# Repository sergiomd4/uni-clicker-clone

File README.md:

UNI Clicker Clone
========================================

UNI Clicker is a compact development board designed as a complete solution. It contains a MCU Card socket, four mikroBUS sockets for Click boards connectivity and power management. 

Its core is a MCU Card socket that allows UNI Clicker to use different microcontrollers mounted on a standardized MCU Card. The MCU Card can be connected to the UNI Clicker by two 168-pin mezzanine connectors, one male and one female. This MCU Card supports architectures such as ARM, PIC32, dsPIC, PIC, AVR, Microchip, ST, NXP, TI and more.

UNI Clicker can be powered on by a small switch at the edge of the board. Therefore, the PSU (Power Supply Unit) module will be enabled and the power will be distributed. The PWR LED indicates that the board is ON.

Repository Contents
-------------------

* **/Production** - Gerber files, drill files, BOM, CPL file
* **/Hardware** - KiCad PCB files, footprints library
* **/Documents** - Schematics pdf

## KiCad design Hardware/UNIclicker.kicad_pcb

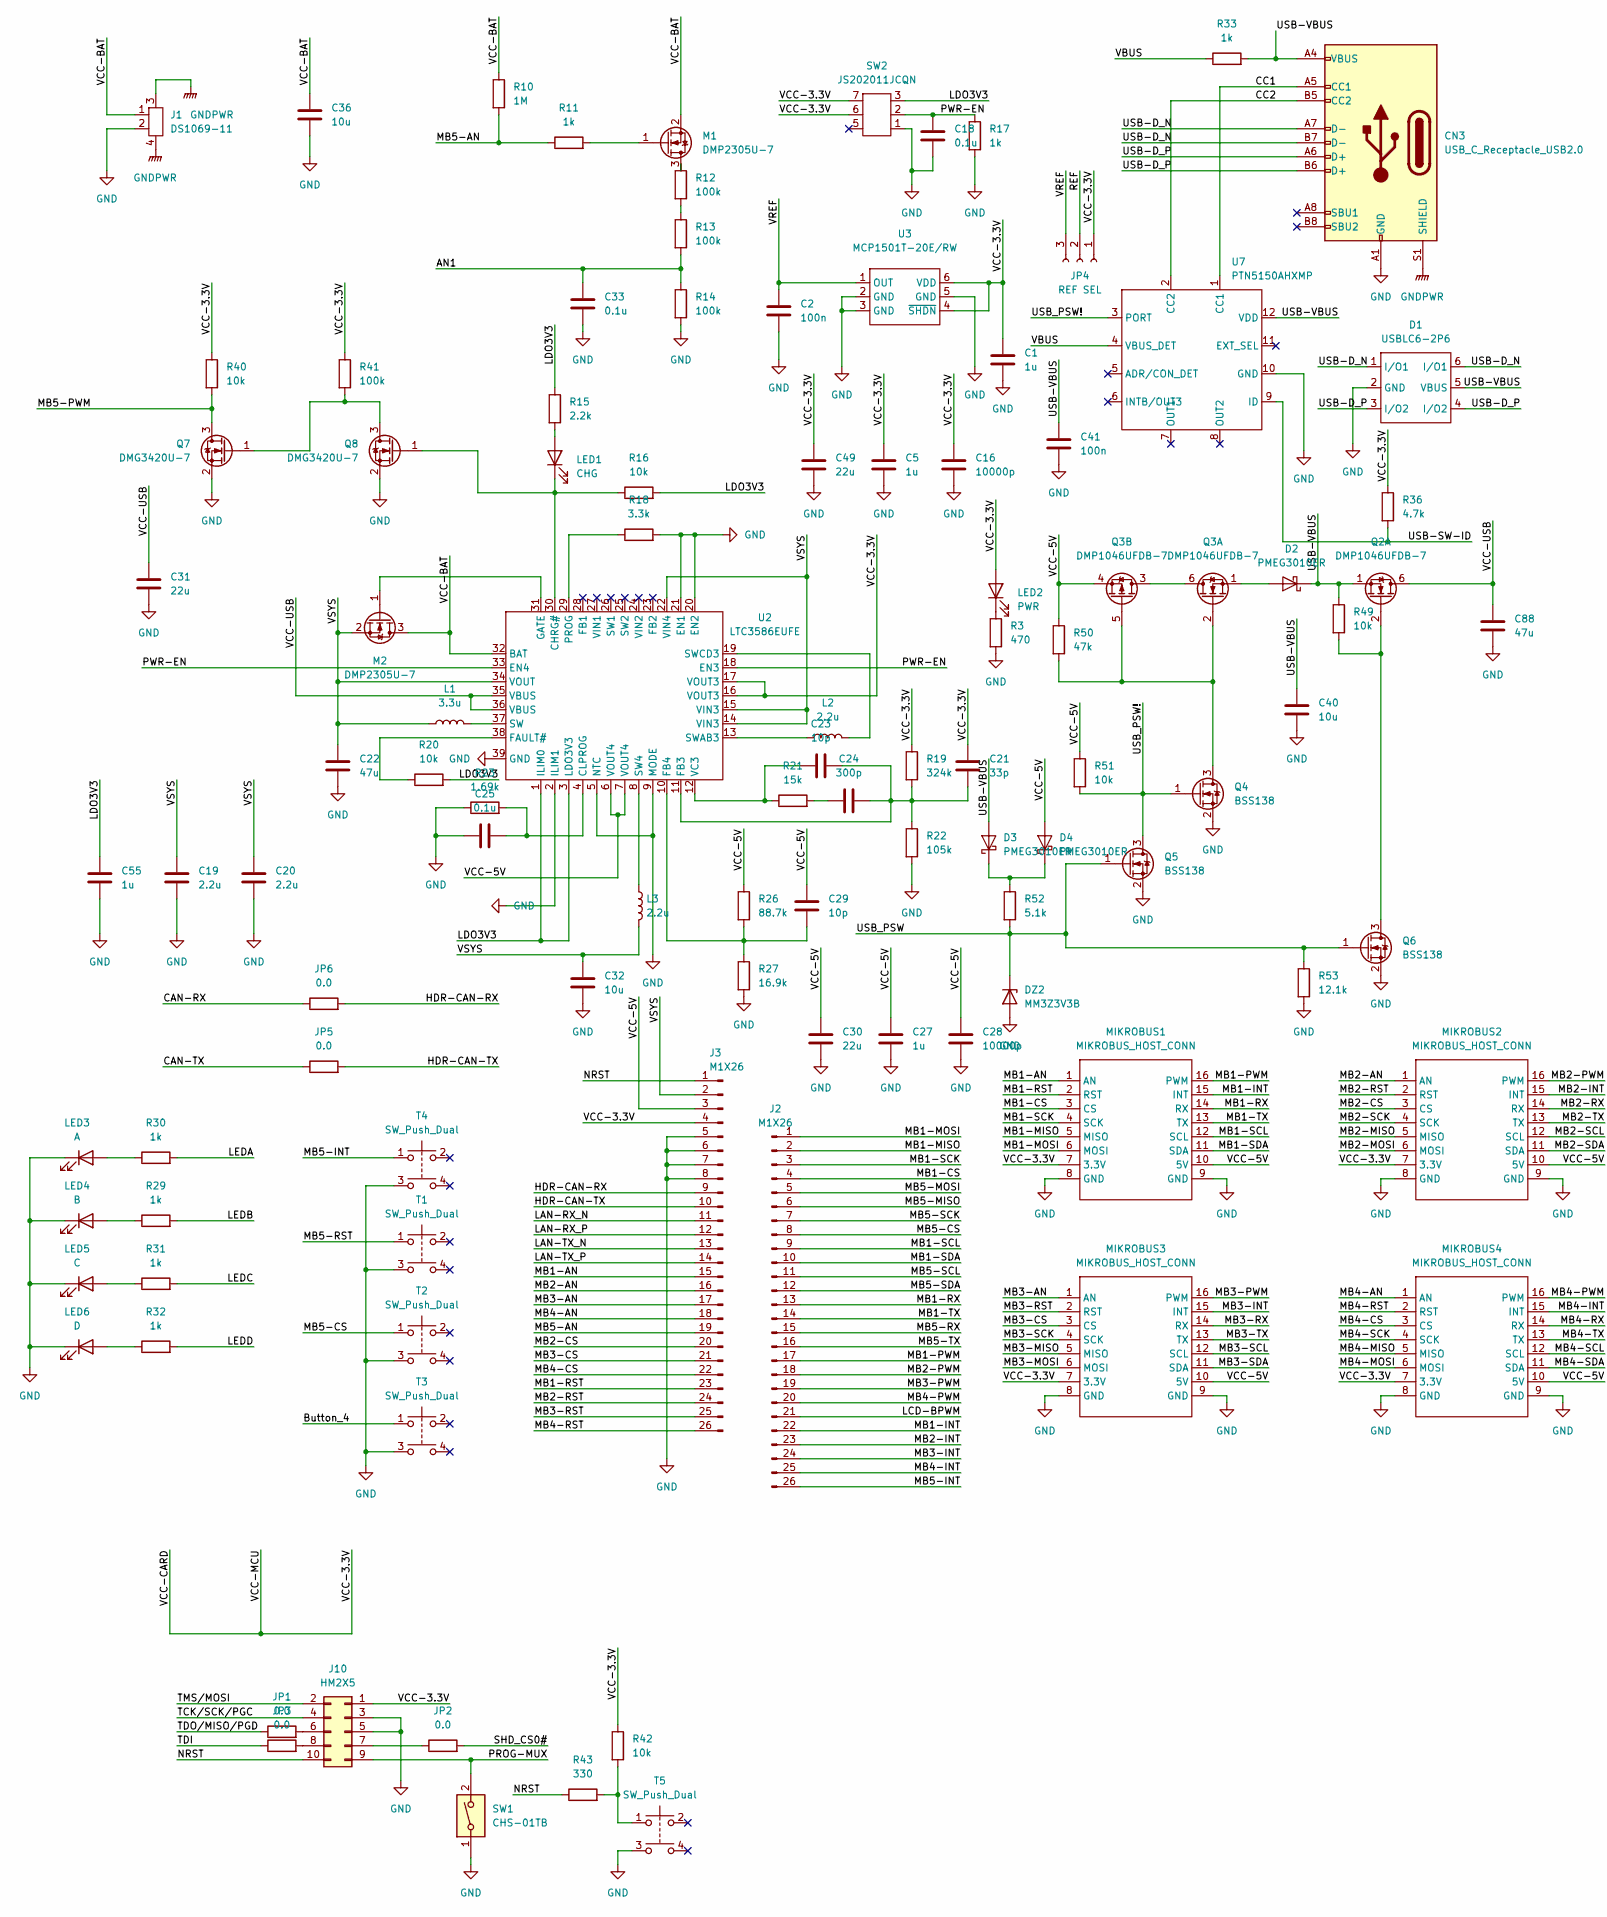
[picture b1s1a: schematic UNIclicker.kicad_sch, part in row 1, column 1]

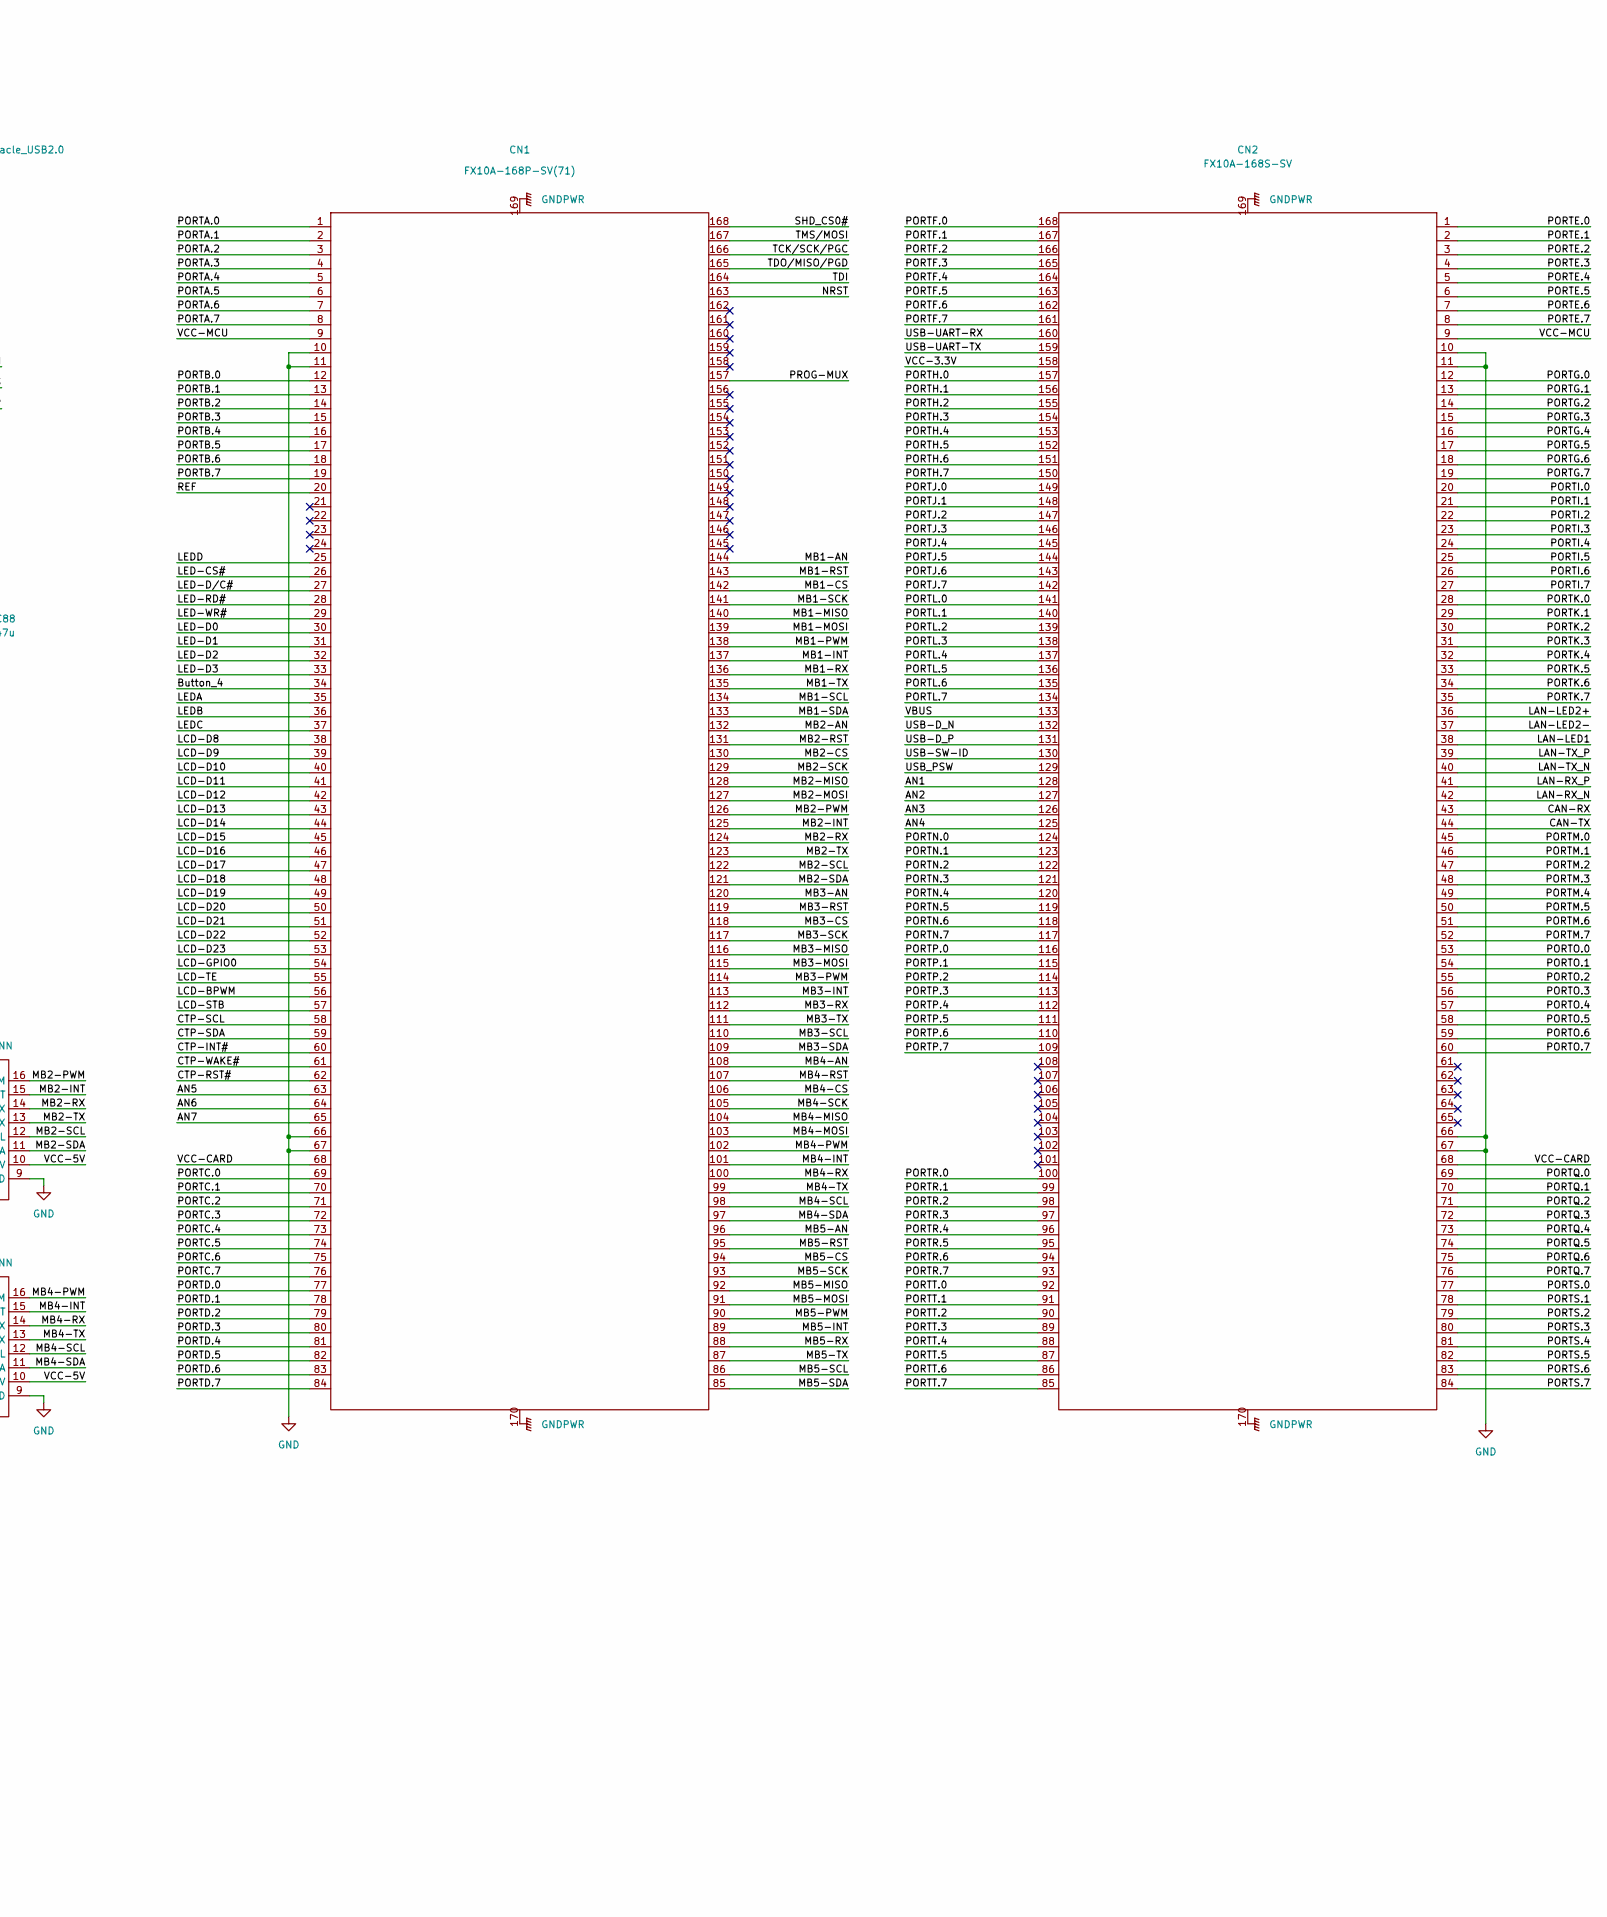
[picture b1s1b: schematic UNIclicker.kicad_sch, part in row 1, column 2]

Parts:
C1, C5, C27, C55: 1u; C_0402_1005Metric; LCSC Part Number C14445
C2, C41: 100n; C_0402_1005Metric; LCSC Part Number C60474
C16, C28: 10000p; C_0402_1005Metric; LCSC Part Number C60133
C18, C25, C33: 0.1u; C_0402_1005Metric; LCSC Part Number C1525
C19, C20: 2.2u; C_0402_1005Metric; LCSC Part Number C107369
C21: 33p; C_0402_1005Metric; LCSC Part Number C1562
C22, C88: 47u; C_0805_2012Metric; LCSC Part Number C16780
C23, C29: 10p; C_0402_1005Metric; LCSC Part Number C696913
C24: 300p; C_0402_1005Metric; LCSC Part Number C1534
C30, C31, C49: 22u; C_0603_1608Metric; LCSC Part Number C59461
C32, C36, C40: 10u; C_0603_1608Metric; LCSC Part Number C19702
CN1: FX10A-168P-SV(71); LCSC Part Number C598050
CN2: FX10A-168S-SV; LCSC Part Number C598051
CN3: USB_C_Receptacle_USB2.0; USB_C_Receptacle_HRO_TYPE-C-31-M-12; LCSC Part Number C709357
D1: USBLC6-2P6; LCSC Part Number C2827693
D2, D3, D4: PMEG3010ER; Nexperia_CFP3_SOD-123W; LCSC Part Number C456106
DZ2: MM3Z3V3B; LCSC Part Number C556407
J1: DS1069-11; LCSC Part Number C160388
J2, J3: M1X26; PinHeader_1x26_P2.54mm_Vertical
J10: HM2X5; J10; LCSC Part Number C124391
JP1, JP2, JP3, JP5, JP6: 0.0; R_0603_1608Metric; LCSC Part Number C122704
JP4: REF SEL; JP4; LCSC Part Number C122704
L1: 3.3u; L1; LCSC Part Number C15269
L2, L3: 2.2u; L1; LCSC Part Number C38117
LED1: CHG; LED_0402_1005Metric; LCSC Part Number C965790
LED2: PWR; LED_0402_1005Metric; LCSC Part Number C434446
LED3: A; LED_0402_1005Metric; LCSC Part Number C965790
LED4: B; LED_0402_1005Metric; LCSC Part Number C965790
LED5: C; LED_0402_1005Metric; LCSC Part Number C965790
LED6: D; LED_0402_1005Metric; LCSC Part Number C965790
M1, M2: DMP2305U-7; SOT-23; LCSC Part Number C85097
MIKROBUS1, MIKROBUS2, MIKROBUS3, MIKROBUS4: MIKROBUS_HOST_CONN; SOCKET MIKROBUS
Q2, Q3: DMP1046UFDB-7; SOT-363_SC-70-6; LCSC Part Number C131781
Q4, Q5, Q6: BSS138; SOT-23; LCSC Part Number C112239
Q7, Q8: DMG3420U-7; SOT-23; LCSC Part Number C154722
R3: 470; R_0402_1005Metric; LCSC Part Number C25117
R10: 1M; R_0402_1005Metric; LCSC Part Number C93949
R11, R17, R29, R30, R31, R32, R33: 1k; R_0402_1005Metric; LCSC Part Number C226166
R12, R13, R14, R41: 100k; R_0402_1005Metric; LCSC Part Number C25741
R15: 2.2k; R_0402_1005Metric; LCSC Part Number C25879
R16, R20, R40, R42, R49, R51: 10k; R_0402_1005Metric; LCSC Part Number C140214
R18: 3.3k; R_0402_1005Metric; LCSC Part Number C25890
R19: 324k; R_0402_1005Metric; LCSC Part Number C113480
R21: 15k; R_0402_1005Metric; LCSC Part Number C25756
R22: 105k; R_0402_1005Metric; LCSC Part Number C25742
R23: 1.69k; R_0402_1005Metric; LCSC Part Number C25870
R26: 88.7k; R_0402_1005Metric; LCSC Part Number C25922
R27: 16.9k; R_0402_1005Metric; LCSC Part Number C25858
R36: 4.7k; R_0402_1005Metric; LCSC Part Number C304616
R43: 330; R_0402_1005Metric; LCSC Part Number C12246
R50: 47k; R_0402_1005Metric; LCSC Part Number C25563
R52: 5.1k; R_0402_1005Metric; LCSC Part Number C25905
R53: 12.1k; R_0402_1005Metric; LCSC Part Number C25852
SW1: CHS-01TB; LCSC Part Number C54948
SW2: JS202011JCQN; LCSC Part Number C221665
T1, T2, T3, T4, T5: SW_Push_Dual; PUSH_BUTTON; LCSC Part Number C127509
U2: LTC3586EUFE; QFN-38-1EP_4x6mm_P0.4mm_EP2.65x4.65mm
U3: MCP1501T-20E/RW; SOT-23-6
U7: PTN5150AHXMP

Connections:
/AN1: C33.1, CN2.128, R13.2, R14.1
/AN2: CN2.127
/AN3: CN2.126
/AN4: CN2.125
/AN5: CN1.63
/AN6: CN1.64
/AN7: CN1.65
/Button_4: CN1.34, T3.1
/CAN-RX: CN2.43, JP6.1
/CAN-TX: CN2.44, JP5.1
/CC1: CN3.A5 (CC1), U7.1 (CC1)
/CC2: CN3.B5 (CC2), U7.2 (CC2)
/CTP-INT#: CN1.60
/CTP-RST#: CN1.62
/CTP-SCL: CN1.58
/CTP-SDA: CN1.59
/CTP-WAKE#: CN1.61
/HDR-CAN-RX: J3.9, JP6.2
/HDR-CAN-TX: J3.10, JP5.2
/LAN-LED1: CN2.38
/LAN-LED2+: CN2.36
/LAN-LED2-: CN2.37
/LAN-RX_N: CN2.42, J3.11
/LAN-RX_P: CN2.41, J3.12
/LAN-TX_N: CN2.40, J3.13
/LAN-TX_P: CN2.39, J3.14
/LCD-BPWM: CN1.56, J2.21
/LCD-D8: CN1.38
/LCD-D9: CN1.39
/LCD-D10: CN1.40
/LCD-D11: CN1.41
/LCD-D12: CN1.42
/LCD-D13: CN1.43
/LCD-D14: CN1.44
/LCD-D15: CN1.45
/LCD-D16: CN1.46
/LCD-D17: CN1.47
/LCD-D18: CN1.48
/LCD-D19: CN1.49
/LCD-D20: CN1.50
/LCD-D21: CN1.51
/LCD-D22: CN1.52
/LCD-D23: CN1.53
/LCD-GPIO0: CN1.54
/LCD-STB: CN1.57
/LCD-TE: CN1.55
/LDO3V3: C55.1, R15.1, R16.2, R20.2, SW2.3, U2.1 (ILIM0), U2.3 (LDO3V3)
/LED-CS#: CN1.26
/LED-D0: CN1.30
/LED-D1: CN1.31
/LED-D2: CN1.32
/LED-D3: CN1.33
/LED-D/C#: CN1.27
/LED-RD#: CN1.28
/LED-WR#: CN1.29
/LEDA: CN1.35, R30.2
/LEDB: CN1.36, R29.2
/LEDC: CN1.37, R31.2
/LEDD: CN1.25, R32.2
/MB1-AN: CN1.144, J3.15, MIKROBUS1.1 (AN)
/MB1-CS: CN1.142, J2.4, MIKROBUS1.3 (CS)
/MB1-INT: CN1.137, J2.22, MIKROBUS1.15 (INT)
/MB1-MISO: CN1.140, J2.2, MIKROBUS1.5 (MISO)
/MB1-MOSI: CN1.139, J2.1, MIKROBUS1.6 (MOSI)
/MB1-PWM: CN1.138, J2.17, MIKROBUS1.16 (PWM)
/MB1-RST: CN1.143, J3.23, MIKROBUS1.2 (RST)
/MB1-RX: CN1.136, J2.13, MIKROBUS1.14 (RX)
/MB1-SCK: CN1.141, J2.3, MIKROBUS1.4 (SCK)
/MB1-SCL: CN1.134, J2.9, MIKROBUS1.12 (SCL)
/MB1-SDA: CN1.133, J2.10, MIKROBUS1.11 (SDA)
/MB1-TX: CN1.135, J2.14, MIKROBUS1.13 (TX)
/MB2-AN: CN1.132, J3.16, MIKROBUS2.1 (AN)
/MB2-CS: CN1.130, J3.20, MIKROBUS2.3 (CS)
/MB2-INT: CN1.125, J2.23, MIKROBUS2.15 (INT)
/MB2-MISO: CN1.128, MIKROBUS2.5 (MISO)
/MB2-MOSI: CN1.127, MIKROBUS2.6 (MOSI)
/MB2-PWM: CN1.126, J2.18, MIKROBUS2.16 (PWM)
/MB2-RST: CN1.131, J3.24, MIKROBUS2.2 (RST)
/MB2-RX: CN1.124, MIKROBUS2.14 (RX)
/MB2-SCK: CN1.129, MIKROBUS2.4 (SCK)
/MB2-SCL: CN1.122, MIKROBUS2.12 (SCL)
/MB2-SDA: CN1.121, MIKROBUS2.11 (SDA)
/MB2-TX: CN1.123, MIKROBUS2.13 (TX)
/MB3-AN: CN1.120, J3.17, MIKROBUS3.1 (AN)
/MB3-CS: CN1.118, J3.21, MIKROBUS3.3 (CS)
/MB3-INT: CN1.113, J2.24, MIKROBUS3.15 (INT)
/MB3-MISO: CN1.116, MIKROBUS3.5 (MISO)
/MB3-MOSI: CN1.115, MIKROBUS3.6 (MOSI)
/MB3-PWM: CN1.114, J2.19, MIKROBUS3.16 (PWM)
/MB3-RST: CN1.119, J3.25, MIKROBUS3.2 (RST)
/MB3-RX: CN1.112, MIKROBUS3.14 (RX)
/MB3-SCK: CN1.117, MIKROBUS3.4 (SCK)
/MB3-SCL: CN1.110, MIKROBUS3.12 (SCL)
/MB3-SDA: CN1.109, MIKROBUS3.11 (SDA)
/MB3-TX: CN1.111, MIKROBUS3.13 (TX)
/MB4-AN: CN1.108, J3.18, MIKROBUS4.1 (AN)
/MB4-CS: CN1.106, J3.22, MIKROBUS4.3 (CS)
/MB4-INT: CN1.101, J2.25, MIKROBUS4.15 (INT)
/MB4-MISO: CN1.104, MIKROBUS4.5 (MISO)
/MB4-MOSI: CN1.103, MIKROBUS4.6 (MOSI)
/MB4-PWM: CN1.102, J2.20, MIKROBUS4.16 (PWM)
/MB4-RST: CN1.107, J3.26, MIKROBUS4.2 (RST)
/MB4-RX: CN1.100, MIKROBUS4.14 (RX)
/MB4-SCK: CN1.105, MIKROBUS4.4 (SCK)
/MB4-SCL: CN1.98, MIKROBUS4.12 (SCL)
/MB4-SDA: CN1.97, MIKROBUS4.11 (SDA)
/MB4-TX: CN1.99, MIKROBUS4.13 (TX)
/MB5-AN: CN1.96, J3.19, R10.2, R11.1
/MB5-CS: CN1.94, J2.8, T2.1
/MB5-INT: CN1.89, J2.26, T4.1
/MB5-MISO: CN1.92, J2.6
/MB5-MOSI: CN1.91, J2.5
/MB5-PWM: CN1.90, Q7.3 (D), R40.2
/MB5-RST: CN1.95, T1.1
/MB5-RX: CN1.88, J2.15
/MB5-SCK: CN1.93, J2.7
/MB5-SCL: CN1.86, J2.11
/MB5-SDA: CN1.85, J2.12
/MB5-TX: CN1.87, J2.16
/NRST: CN1.163, J3.1, J10.10, R43.1
/PORTA.0: CN1.1
/PORTA.1: CN1.2
/PORTA.2: CN1.3
/PORTA.3: CN1.4
/PORTA.4: CN1.5
/PORTA.5: CN1.6
/PORTA.6: CN1.7
/PORTA.7: CN1.8
/PORTB.0: CN1.12
/PORTB.1: CN1.13
/PORTB.2: CN1.14
/PORTB.3: CN1.15
/PORTB.4: CN1.16
/PORTB.5: CN1.17
/PORTB.6: CN1.18
/PORTB.7: CN1.19
/PORTC.0: CN1.69
/PORTC.1: CN1.70
/PORTC.2: CN1.71
/PORTC.3: CN1.72
/PORTC.4: CN1.73
/PORTC.5: CN1.74
/PORTC.6: CN1.75
/PORTC.7: CN1.76
/PORTD.0: CN1.77
/PORTD.1: CN1.78
/PORTD.2: CN1.79
/PORTD.3: CN1.80
/PORTD.4: CN1.81
/PORTD.5: CN1.82
/PORTD.6: CN1.83
/PORTD.7: CN1.84
/PORTE.0: CN2.1
/PORTE.1: CN2.2
/PORTE.2: CN2.3
/PORTE.3: CN2.4
/PORTE.4: CN2.5
/PORTE.5: CN2.6
/PORTE.6: CN2.7
/PORTE.7: CN2.8
/PORTF.0: CN2.168
/PORTF.1: CN2.167
/PORTF.2: CN2.166
/PORTF.3: CN2.165
/PORTF.4: CN2.164
/PORTF.5: CN2.163
/PORTF.6: CN2.162
/PORTF.7: CN2.161
/PORTG.0: CN2.12
/PORTG.1: CN2.13
/PORTG.2: CN2.14
/PORTG.3: CN2.15
/PORTG.4: CN2.16
/PORTG.5: CN2.17
/PORTG.6: CN2.18
/PORTG.7: CN2.19
/PORTH.0: CN2.157
/PORTH.1: CN2.156
/PORTH.2: CN2.155
/PORTH.3: CN2.154
/PORTH.4: CN2.153
/PORTH.5: CN2.152
/PORTH.6: CN2.151
/PORTH.7: CN2.150
/PORTI.0: CN2.20
/PORTI.1: CN2.21
/PORTI.2: CN2.22
/PORTI.3: CN2.23
/PORTI.4: CN2.24
/PORTI.5: CN2.25
/PORTI.6: CN2.26
/PORTI.7: CN2.27
/PORTJ.0: CN2.149
/PORTJ.1: CN2.148
/PORTJ.2: CN2.147
/PORTJ.3: CN2.146
/PORTJ.4: CN2.145
/PORTJ.5: CN2.144
/PORTJ.6: CN2.143
/PORTJ.7: CN2.142
/PORTK.0: CN2.28
/PORTK.1: CN2.29
/PORTK.2: CN2.30
/PORTK.3: CN2.31
/PORTK.4: CN2.32
/PORTK.5: CN2.33
/PORTK.6: CN2.34
/PORTK.7: CN2.35
/PORTL.0: CN2.141
/PORTL.1: CN2.140
/PORTL.2: CN2.139
/PORTL.3: CN2.138
/PORTL.4: CN2.137
/PORTL.5: CN2.136
/PORTL.6: CN2.135
/PORTL.7: CN2.134
/PORTM.0: CN2.45
/PORTM.1: CN2.46
/PORTM.2: CN2.47
/PORTM.3: CN2.48
/PORTM.4: CN2.49
/PORTM.5: CN2.50
/PORTM.6: CN2.51
/PORTM.7: CN2.52
/PORTN.0: CN2.124
/PORTN.1: CN2.123
/PORTN.2: CN2.122
/PORTN.3: CN2.121
/PORTN.4: CN2.120
/PORTN.5: CN2.119
/PORTN.6: CN2.118
/PORTN.7: CN2.117
/PORTO.0: CN2.53
/PORTO.1: CN2.54
/PORTO.2: CN2.55
/PORTO.3: CN2.56
/PORTO.4: CN2.57
/PORTO.5: CN2.58
/PORTO.6: CN2.59
/PORTO.7: CN2.60
/PORTP.0: CN2.116
/PORTP.1: CN2.115
/PORTP.2: CN2.114
/PORTP.3: CN2.113
/PORTP.4: CN2.112
/PORTP.5: CN2.111
/PORTP.6: CN2.110
/PORTP.7: CN2.109
/PORTQ.0: CN2.69
/PORTQ.1: CN2.70
/PORTQ.2: CN2.71
/PORTQ.3: CN2.72
/PORTQ.4: CN2.73
/PORTQ.5: CN2.74
/PORTQ.6: CN2.75
/PORTQ.7: CN2.76
/PORTR.0: CN2.100
/PORTR.1: CN2.99
/PORTR.2: CN2.98
/PORTR.3: CN2.97
/PORTR.4: CN2.96
/PORTR.5: CN2.95
/PORTR.6: CN2.94
/PORTR.7: CN2.93
/PORTS.0: CN2.77
/PORTS.1: CN2.78
/PORTS.2: CN2.79
/PORTS.3: CN2.80
/PORTS.4: CN2.81
/PORTS.5: CN2.82
/PORTS.6: CN2.83
/PORTS.7: CN2.84
/PORTT.0: CN2.92
/PORTT.1: CN2.91
/PORTT.2: CN2.90
/PORTT.3: CN2.89
/PORTT.4: CN2.88
/PORTT.5: CN2.87
/PORTT.6: CN2.86
/PORTT.7: CN2.85
/PROG-MUX: CN1.157, J10.9, SW1.2
/PWR-EN: C18.1, R17.1, SW2.2, U2.18 (EN3), U2.33 (EN4)
/REF: CN1.20, JP4.2
/SHD_CS0#: CN1.168, JP2.2
/TCK/SCK/PGC: CN1.166, J10.4
/TDI: CN1.164, JP3.1
/TDO/MISO/PGD: CN1.165, JP1.1
/TMS/MOSI: CN1.167, J10.2
/USB-D_N: CN2.132, CN3.A7 (D-), CN3.B7 (D-), D1.1 (I/O1), D1.6 (I/O1)
/USB-D_P: CN2.131, CN3.A6 (D+), CN3.B6 (D+), D1.3 (I/O2), D1.4 (I/O2)
/USB-SW-ID: CN2.130, R36.2, U7.9 (ID)
/USB-UART-RX: CN2.160
/USB-UART-TX: CN2.159
/USB-VBUS: C40.1, C41.1, CN3.A4 (VBUS), CN3.A9 (VBUS), CN3.B4 (VBUS), CN3.B9 (VBUS), D1.5 (VBUS), D2.1 (K), D3.2 (A), Q2.1 (SN), R33.2, R49.1, U7.12 (VDD)
/USB_PSW: CN2.129, DZ2.1 (K), Q5.1 (G), Q6.1 (G), R52.2, R53.1
/USB_PSW!: Q4.1 (G), Q5.3 (D), R51.2, U7.3 (PORT)
/VBUS: CN2.133, R33.1, U7.4 (VBUS_DET)
/VCC-3.3V: C1.1, C5.1, C16.1, C21.1, C49.1, CN1.9, CN1.68, CN2.9, CN2.68, CN2.158, J3.4, J10.1, JP4.1, LED2.2 (A), MIKROBUS1.7 (3.3V), MIKROBUS2.7 (3.3V), MIKROBUS3.7 (3.3V), MIKROBUS4.7 (3.3V), R19.1, R36.1, R40.1, R41.1, R42.1, SW2.6, SW2.7, U2.16 (VOUT3), U2.17 (VOUT3), U3.4 (~SHDN), U3.6 (VDD)
/VCC-5V: C27.1, C28.1, C29.1, C30.1, D4.2 (A), J3.3, MIKROBUS1.10 (5V), MIKROBUS2.10 (5V), MIKROBUS3.10 (5V), MIKROBUS4.10 (5V), Q3.4 (SP), R26.1, R50.1, R51.1, U2.6 (VOUT4), U2.7 (VOUT4)
/VCC-BAT: C36.1, J1.1, M1.2 (S), M2.3 (D), R10.1, U2.32 (BAT)
/VCC-USB: C31.1, C88.1, Q2.6 (DN), U2.35 (VBUS), U2.36 (VBUS)
/VREF: C2.1, JP4.3, U3.1 (OUT)
/VSYS: C19.1, C20.1, C22.1, C32.1, J3.2, L1.1, L3.2, M2.2 (S), U2.14 (VIN3), U2.15 (VIN3), U2.22 (VIN4), U2.34 (VOUT)
GND: C1.2, C2.2, C5.2, C16.2, C18.2, C19.2, C20.2, C22.2, C25.1, C27.2, C28.2, C30.2, C31.2, C32.2, C33.2, C36.2, C40.2, C41.2, C49.2, C55.2, C88.2, CN1.10, CN1.11, CN1.66, CN1.67, CN2.10, CN2.11, CN2.66, CN2.67, CN3.A1 (GND), CN3.A12 (GND), CN3.B1 (GND), CN3.B12 (GND), D1.2 (GND), DZ2.2 (A), J1.2, J3.5, J3.6, J3.7, J3.8, J10.3, J10.5, LED3.1 (K), LED4.1 (K), LED5.1 (K), LED6.1 (K), MIKROBUS1.8 (GND), MIKROBUS1.9 (GND), MIKROBUS2.8 (GND), MIKROBUS2.9 (GND), MIKROBUS3.8 (GND), MIKROBUS3.9 (GND), MIKROBUS4.8 (GND), MIKROBUS4.9 (GND), Q4.2 (S), Q5.2 (S), Q6.2 (S), Q7.2 (S), Q8.2 (S), R3.2, R14.2, R17.2, R18.2, R22.2, R23.1, R27.2, R53.2, SW1.1, SW2.1, T1.3, T2.3, T3.3, T4.3, T5.3, U2.2 (ILIM1), U2.5 (NTC), U2.9 (MODE), U2.20 (EN2), U2.21 (EN1), U2.39 (GND), U3.2 (GND), U3.3 (GND), U3.5 (GND), U7.10 (GND)
GNDPWR: CN1.169, CN1.170, CN2.169, CN2.170, CN3.S1 (SHIELD), J1.3, J1.4
unnamed: C21.2, C23.2, C24.2, R19.2, R22.1, U2.11 (FB3)
unnamed: C23.1, R21.1, U2.12 (VC3)
unnamed: C24.1, R21.2
unnamed: C25.2, R23.2, U2.4 (CLPROG)
unnamed: C29.2, R26.2, R27.1, U2.10 (FB4)
unnamed: D2.2 (A), Q3.1 (SN)
unnamed: D3.1 (K), D4.1 (K), R52.1
unnamed: J10.6, JP1.2
unnamed: J10.7, JP2.1
unnamed: J10.8, JP3.2
unnamed: L1.2, U2.37 (SW)
unnamed: L2.1, U2.13 (SWAB3)
unnamed: L2.2, U2.19 (SWCD3)
unnamed: L3.1, U2.8 (SW4)
unnamed: LED1.1 (K), Q8.1 (G), R16.1, U2.30 (CHRG#)
unnamed: LED1.2 (A), R15.2
unnamed: LED2.1 (K), R3.1
unnamed: LED3.2 (A), R30.1
unnamed: LED4.2 (A), R29.1
unnamed: LED5.2 (A), R31.1
unnamed: LED6.2 (A), R32.1
unnamed: M1.1 (G), R11.2
unnamed: M1.3 (D), R12.1
unnamed: M2.1 (G), U2.31 (GATE)
unnamed: Q2.2 (GN), Q6.3 (D), R49.2
unnamed: Q3.2 (GN), Q3.5 (GP), Q4.3 (D), R50.2
unnamed: Q3.3 (DP), Q3.6 (DN)
unnamed: Q7.1 (G), Q8.3 (D), R41.2
unnamed: R12.2, R13.1
unnamed: R18.1, U2.29 (PROG)
unnamed: R20.1, U2.38 (FAULT#)
unnamed: R42.2, R43.2, T5.1

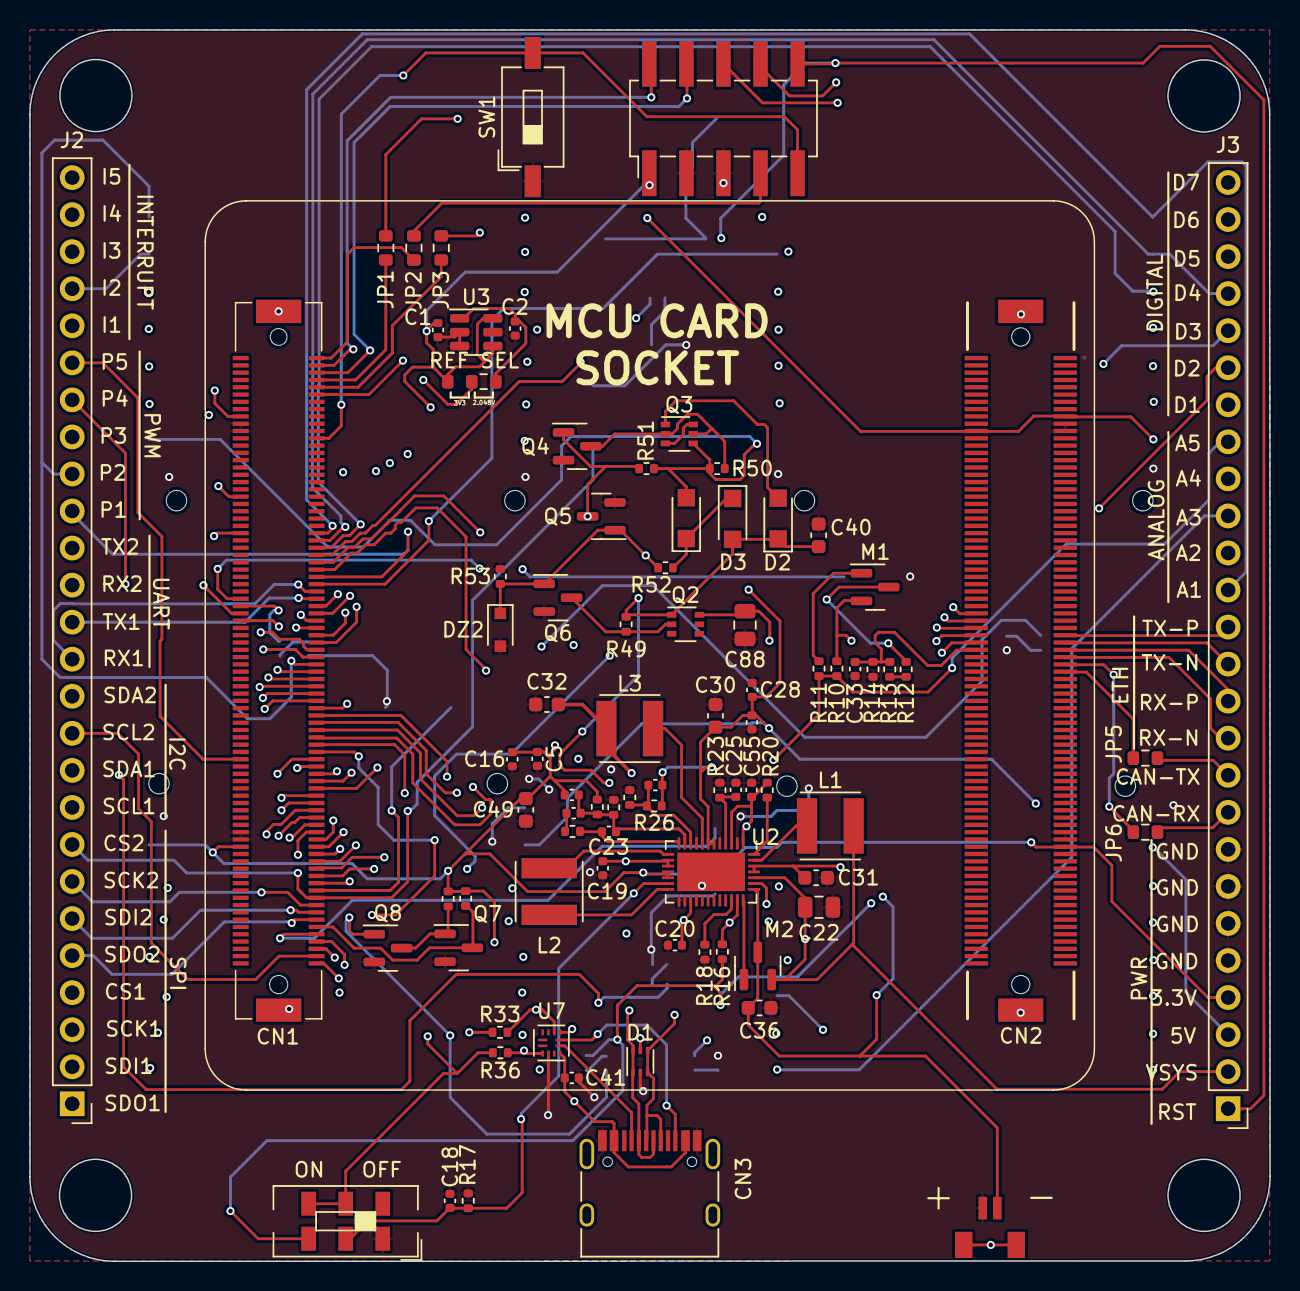
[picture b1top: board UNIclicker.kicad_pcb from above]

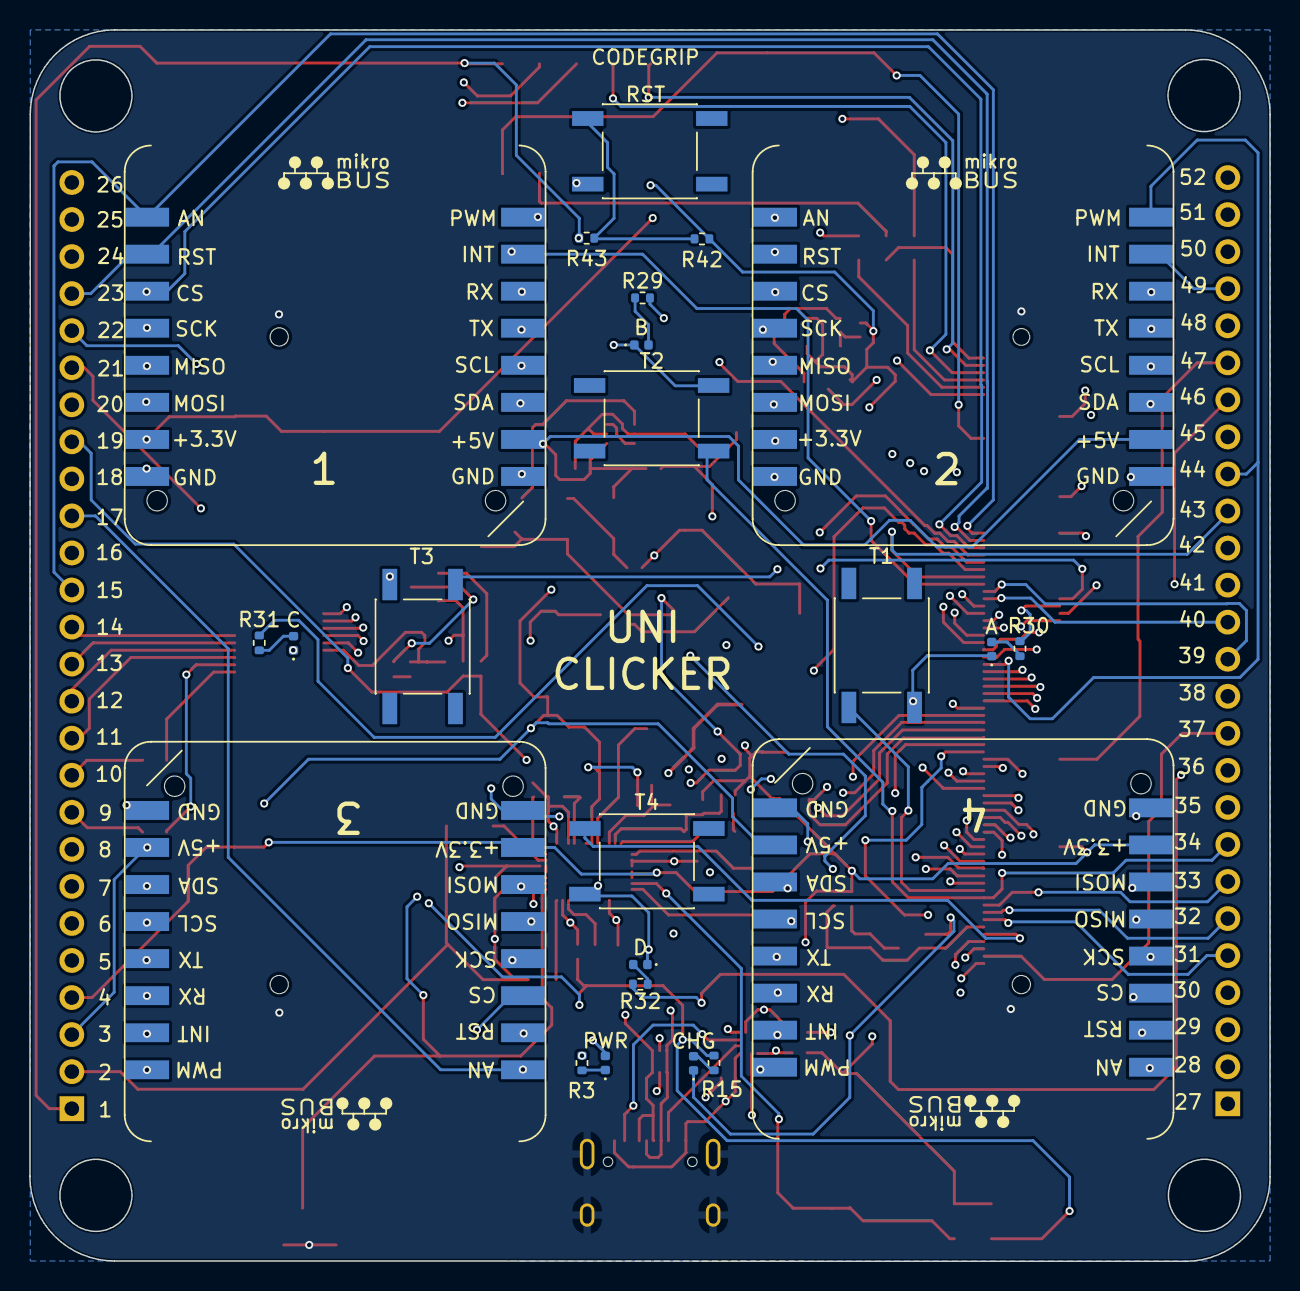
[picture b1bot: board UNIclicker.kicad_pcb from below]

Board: 4 copper layers, 85.0 x 84.4 mm, 107 parts (23 on the bottom side), 134 nets.

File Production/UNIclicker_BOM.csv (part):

"Source:","C:\Users\Sergio\Documents\EOS\UNIclicker\UNIclicker\UNIclicker.kicad_sch"
"Date:","29/08/2022 18:50:23"
"Tool:","Eeschema (6.0.7)"
"Generator:","C:\Program Files\KiCad\6.0\bin\scripting\plugins/bom_csv_grouped_by_value.py"
"Component Count:","101"

"Individual Components:"

"Item","Qty","Reference(s)","Value","LibPart","Footprint","Datasheet","LCSC Part Number"
"","","C1","1u","Device:C","Capacitor_SMD:C_0402_1005Metric","~","C14445"
"","","C2","100n","Device:C","Capacitor_SMD:C_0402_1005Metric","~","C60474"
"","","C5","1u","Device:C","Capacitor_SMD:C_0402_1005Metric","~","C14445"
"","","C16","10000p","Device:C","Capacitor_SMD:C_0402_1005Metric","~","C60133"
"","","C18","0.1u","Device:C","Capacitor_SMD:C_0402_1005Metric","~","C1525"
"","","C19","2.2u","Device:C","Capacitor_SMD:C_0402_1005Metric","~","C107369"
"","","C20","2.2u","Device:C","Capacitor_SMD:C_0402_1005Metric","~","C107369"
"","","C21","33p","Device:C","Capacitor_SMD:C_0402_1005Metric","~","C1562"
"","","C22","47u","Device:C","Capacitor_SMD:C_0805_2012Metric","~","C16780"
"","","C23","10p","Device:C","Capacitor_SMD:C_0402_1005Metric","~","C696913"
"","","C24","300p","Device:C","Capacitor_SMD:C_0402_1005Metric","~","C1534"
"","","C25","0.1u","Device:C","Capacitor_SMD:C_0402_1005Metric","~","C1525"
"","","C27","1u","Device:C","Capacitor_SMD:C_0402_1005Metric","~","C14445"
"","","C28","10000p","Device:C","Capacitor_SMD:C_0402_1005Metric","~","C60133"
"","","C29","10p","Device:C","Capacitor_SMD:C_0402_1005Metric","~","C696913"
"","","C30","22u","Device:C","Capacitor_SMD:C_0603_1608Metric","~","C59461"
"","","C31","22u","Device:C","Capacitor_SMD:C_0603_1608Metric","~","C59461"
"","","C32","10u","Device:C","Capacitor_SMD:C_0603_1608Metric","~","C19702"
"","","C33","0.1u","Device:C","Capacitor_SMD:C_0402_1005Metric","~","C1525"
"","","C36","10u","Device:C","Capacitor_SMD:C_0603_1608Metric","~","C19702"
"","","C40","10u","Device:C","Capacitor_SMD:C_0603_1608Metric","~","C19702"
"","","C41","100n","Device:C","Capacitor_SMD:C_0402_1005Metric","~","C60474"
"","","C49","22u","Device:C","Capacitor_SMD:C_0603_1608Metric","~","C59461"
"","","C55","1u","Device:C","Capacitor_SMD:C_0402_1005Metric","~","C14445"
"","","C88","47u","Device:C","Capacitor_SMD:C_0805_2012Metric","~","C16780"
"","","CN1","FX10A-168P-SV(71)","UNIclicker:MCU_CARD_SOCKET","EOS:FX10A-168P-SV(71)","","C598050"
"","","CN2","FX10A-168S-SV","UNIclicker:MCU_CARD_SOCKET","EOS:FX10A-168S-SV","","C598051"
"","","CN3","USB_C_Receptacle_USB2.0","Connector:USB_C_Receptacle_USB2.0","Connector_USB:USB_C_Receptacle_HRO_TYPE-C-31-M-12","https://www.usb.org/sites/default/files/documents/usb_type-c.zip","C709357"
"","","D1","USBLC6-2P6","UNIclicker:USBLC6-2P6","EOS:USBLC6-2P6","","C2827693"
"","","D2","PMEG3010ER","Diode:PMEG3010ER","Diode_SMD:Nexperia_CFP3_SOD-123W","https://assets.nexperia.com/documents/data-sheet/PMEG3010ER.pdf","C456106"
"","","D3","PMEG3010ER","Diode:PMEG3010ER","Diode_SMD:Nexperia_CFP3_SOD-123W","https://assets.nexperia.com/documents/data-sheet/PMEG3010ER.pdf","C456106"
"","","D4","PMEG3010ER","Diode:PMEG3010ER","Diode_SMD:Nexperia_CFP3_SOD-123W","https://assets.nexperia.com/documents/data-sheet/PMEG3010ER.pdf","C456106"
"","","DZ2","MM3Z3V3B","Device:D_Zener","EOS:MM3Z3V3B","~","C556407"
"","","J1","DS1069-11","UNIclicker:DS1069-11","EOS:DS1069-11","","C160388"
"","","J10","HM2X5","Connector_Generic:Conn_02x05_Odd_Even","EOS:J10","~","C124391"
"","","JP1","0.0","Device:R","Resistor_SMD:R_0603_1608Metric","~","C122704"
"","","JP2","0.0","Device:R","Resistor_SMD:R_0603_1608Metric","~","C122704"
"","","JP3","0.0","Device:R","Resistor_SMD:R_0603_1608Metric","~","C122704"
"","","JP4","REF SEL","Connector:Conn_01x03_Female","EOS:JP4","~","C122704"
"","","JP5","0.0","Device:R","Resistor_SMD:R_0603_1608Metric","~","C122704"
"","","JP6","0.0","Device:R","Resistor_SMD:R_0603_1608Metric","~","C122704"
"","","L1","3.3u","Device:L","EOS:L1","~","C15269"
"","","L2","2.2u","Device:L","EOS:L1","~","C38117"
"","","L3","2.2u","Device:L","EOS:L1","~","C38117"
"","","LED1","CHG","Device:LED","LED_SMD:LED_0402_1005Metric","~","C965790"
"","","LED2","PWR","Device:LED","LED_SMD:LED_0402_1005Metric","~","C434446"
"","","LED3","A","Device:LED","LED_SMD:LED_0402_1005Metric","~","C965790"
"","","LED4","B","Device:LED","LED_SMD:LED_0402_1005Metric","~","C965790"
"","","LED5","C","Device:LED","LED_SMD:LED_0402_1005Metric","~","C965790"
"","","LED6","D","Device:LED","LED_SMD:LED_0402_1005Metric","~","C965790"
"","","M1","DMP2305U-7","Transistor_FET:2N7002","Package_TO_SOT_SMD:SOT-23","https://www.onsemi.com/pub/Collateral/NDS7002A-D.PDF","C85097"
"","","M2","DMP2305U-7","Transistor_FET:2N7002","Package_TO_SOT_SMD:SOT-23","https://www.onsemi.com/pub/Collateral/NDS7002A-D.PDF","C85097"
"","","Q2","DMP1046UFDB-7","Transistor_FET:BSD235C","Package_TO_SOT_SMD:SOT-363_SC-70-6","https://www.infineon.com/dgdl/Infineon-BSD235C-DS-v02_04-EN.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","C131781"
"","","Q3","DMP1046UFDB-7","Transistor_FET:BSD235C","Package_TO_SOT_SMD:SOT-363_SC-70-6","https://www.infineon.com/dgdl/Infineon-BSD235C-DS-v02_04-EN.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","C131781"
"","","Q4","BSS138","Transistor_FET:BSS138","Package_TO_SOT_SMD:SOT-23","https://www.onsemi.com/pub/Collateral/BSS138-D.PDF","C112239"
"","","Q5","BSS138","Transistor_FET:BSS138","Package_TO_SOT_SMD:SOT-23","https://www.onsemi.com/pub/Collateral/BSS138-D.PDF","C112239"
"","","Q6","BSS138","Transistor_FET:BSS138","Package_TO_SOT_SMD:SOT-23","https://www.onsemi.com/pub/Collateral/BSS138-D.PDF","C112239"
"","","Q7","DMG3420U-7","Transistor_FET:2N7002","Package_TO_SOT_SMD:SOT-23","https://www.onsemi.com/pub/Collateral/NDS7002A-D.PDF","C154722"
"","","Q8","DMG3420U-7","Transistor_FET:2N7002","Package_TO_SOT_SMD:SOT-23","https://www.onsemi.com/pub/Collateral/NDS7002A-D.PDF","C154722"
"","","R3","470","Device:R","Resistor_SMD:R_0402_1005Metric","~","C25117"
"","","R10","1M","Device:R","Resistor_SMD:R_0402_1005Metric","~","C93949"
"","","R11","1k","Device:R","Resistor_SMD:R_0402_1005Metric","~","C226166"
"","","R12","100k","Device:R","Resistor_SMD:R_0402_1005Metric","~","C25741"
"","","R13","100k","Device:R","Resistor_SMD:R_0402_1005Metric","~","C25741"
"","","R14","100k","Device:R","Resistor_SMD:R_0402_1005Metric","~","C25741"
"","","R15","2.2k","Device:R","Resistor_SMD:R_0402_1005Metric","~","C25879"
"","","R16","10k","Device:R","Resistor_SMD:R_0402_1005Metric","~","C140214"
"","","R17","1k","Device:R","Resistor_SMD:R_0402_1005Metric","~","C226166"
"","","R18","3.3k","Device:R","Resistor_SMD:R_0402_1005Metric","~","C25890"
"","","R19","324k","Device:R","Resistor_SMD:R_0402_1005Metric","~","C113480"
"","","R20","10k","Device:R","Resistor_SMD:R_0402_1005Metric","~","C140214"
"","","R21","15k","Device:R","Resistor_SMD:R_0402_1005Metric","~","C25756"
"","","R22","105k","Device:R","Resistor_SMD:R_0402_1005Metric","~","C25742"
"","","R23","1.69k","Device:R","Resistor_SMD:R_0402_1005Metric","~","C25870"
"","","R26","88.7k","Device:R","Resistor_SMD:R_0402_1005Metric","~","C25922"
"","","R27","16.9k","Device:R","Resistor_SMD:R_0402_1005Metric","~","C25858"
"","","R29","1k","Device:R","Resistor_SMD:R_0402_1005Metric","~","C226166"
"","","R30","1k","Device:R","Resistor_SMD:R_0402_1005Metric","~","C226166"
"","","R31","1k","Device:R","Resistor_SMD:R_0402_1005Metric","~","C226166"
"","","R32","1k","Device:R","Resistor_SMD:R_0402_1005Metric","~","C226166"
"","","R33","1k","Device:R","Resistor_SMD:R_0402_1005Metric","~","C226166"
"","","R36","4.7k","Device:R","Resistor_SMD:R_0402_1005Metric","~","C304616"
"","","R40","10k","Device:R","Resistor_SMD:R_0402_1005Metric","~","C140214"
"","","R41","100k","Device:R","Resistor_SMD:R_0402_1005Metric","~","C25741"
"","","R42","10k","Device:R","Resistor_SMD:R_0402_1005Metric","~","C140214"
"","","R43","330","Device:R","Resistor_SMD:R_0402_1005Metric","~","C12246"
"","","R49","10k","Device:R","Resistor_SMD:R_0402_1005Metric","~","C140214"
"","","R50","47k","Device:R","Resistor_SMD:R_0402_1005Metric","~","C25563"
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
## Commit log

2022-09-12 Add schematic
2022-09-12 Add Gerber Files
2022-09-12 Add Drill Files
2022-09-12 Add Images
2022-09-12 Add BOM
2022-09-12 Allow .csv
2022-09-12 Add CPL file
2022-09-12 Add library
2022-09-12 Add KiCad files
2022-09-13 Update images
